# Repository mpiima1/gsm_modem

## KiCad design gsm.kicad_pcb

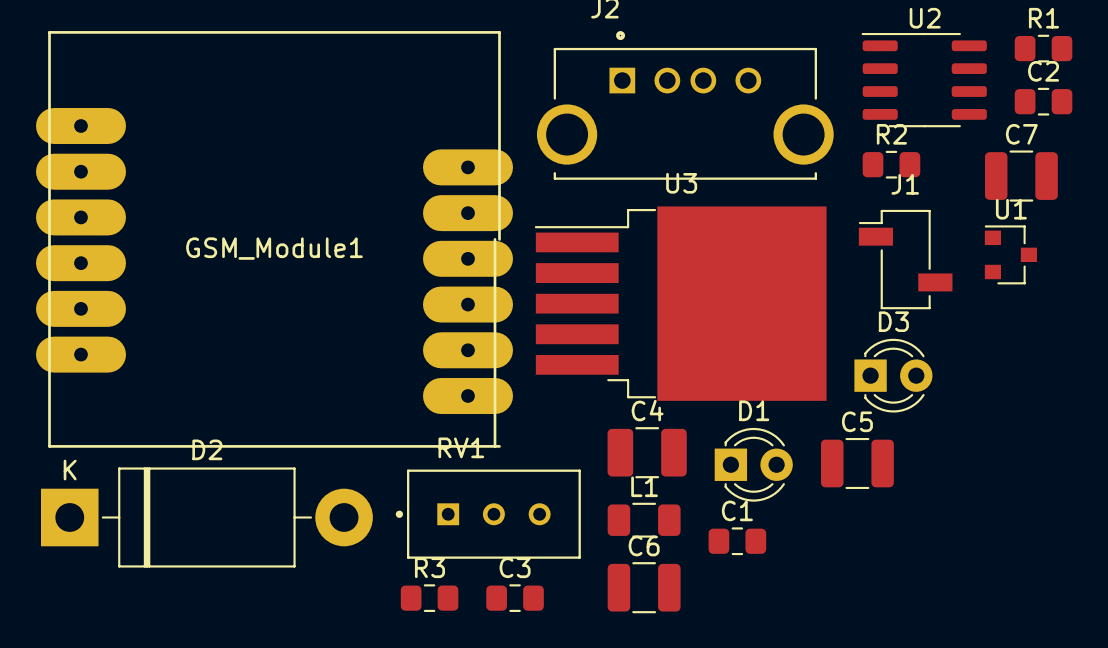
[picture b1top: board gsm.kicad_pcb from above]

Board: 2 copper layers, 21 parts (0 on the bottom side), 14 nets, no tracks yet.

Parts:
C1, C2, C3: 100nF; C_0805_2012Metric_Pad1.15x1.40mm_HandSolder
C4: 100uF; C_1210_3225Metric_Pad1.42x2.65mm_HandSolder
C5, C7: 1uF; C_1210_3225Metric
C6: 220uF; C_1210_3225Metric
D1, D3: LED; LED_D3.0mm
D2: 1N5822; D_DO-201AD_P15.24mm_Horizontal
GSM_Module1: SIM800L
J1: Barrel_Jack; PinSocket_1x02_P2.54mm_Vertical_SMD_Pin1Left
J2: USB-A1VSB6; ONSHORE_USB-A1VSB6
L1: 47uH; L_1206_3216Metric
R1, R3: 1k; R_0805_2012Metric_Pad1.15x1.40mm_HandSolder
R2: 330; R_0805_2012Metric_Pad1.15x1.40mm_HandSolder
RV1: 10K; TRIM_3296W-1-250
U1: LM3480-3.3; SOT-23
U2: CH330N; SOIC-8_3.9x4.9mm_P1.27mm
U3: LM2596S-ADJ; TO-263-5_TabPin3

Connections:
/OUT_4V: C6.1, C7.1, GSM_Module1.2, L1.2, R3.1, RV1.3
GND: C1.2, C2.2, C3.2, C4.2, C5.2, C6.2, C7.2, D1.1, D2.2, D3.1, GSM_Module1.6, J1.2, J2.4, J2.S1, J2.S2, R2.2, U1.3, U2.3, U3.3, U3.5
unnamed: C1.1, J2.1, U1.2
unnamed: C2.1, U2.8
unnamed: C3.1, R1.1, U1.1, U2.5
unnamed: C4.1, C5.1, J1.1, U3.1
unnamed: D1.2, R1.2
unnamed: D2.1, L1.1, U3.2
unnamed: D3.2, R3.2
unnamed: GSM_Module1.4, U2.6
unnamed: GSM_Module1.5, U2.7
unnamed: J2.2, U2.2
unnamed: J2.3, U2.1
unnamed: R2.1, RV1.1, RV1.2, U3.4

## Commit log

2022-10-31 partial image
